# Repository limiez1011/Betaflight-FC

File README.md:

# yecnod F405 V1.1

## Description

open-source (not that anyone would want to use it) 40x40 F405 Flight controller using betaflight software.
## Features

- 3 Universal UARTS
- Dedicated pads for analog VTX
- 9V and 5V Buck converters
- 2x 3.3V LDOS
- Integrated barometer
- LDO and Buck converter status LEDS
- 16MB Blackbox flash
- Full betaflight support
- ICM 42688-P (kind of a flex with how hard they are to get nowadays)
- 4V5 Pads for RX

This is the first revision of the yecnodF405 so expect more features on the 2nd.

[Schematic PDF](https://github.com/user-attachments/files/29501861/20x20.fc.pdf)

## COST

- AROUND 60 USD PER PCB
- AROUND 30 USD FOR 5 PCBS

On my next revision I will try to cut the costs by atleast 40%

## BOM

|   | NAME        | PURPOSE                                | QTY | PRICE  | LINK                                                                                                                                                                                                                                                                                        |
|---|-------------|----------------------------------------|-----|--------|---------------------------------------------------------------------------------------------------------------------------------------------------------------------------------------------------------------------------------------------------------------------------------------------|
| 1 | LCSC        | PASSIVES/ALL IC'S                      | 1   | $73.43 | [LINK](https://www.lcsc.com)                                                                                                                                                                                                                                                                |
| 2 | HOT AIR GUN | SOLDERING                              | 1   | $35    | [LINK](https://www.emag.ro/fier-de-lipit-torta-cu-aer-cald-yihua-8858-iv-a5dc-582e4/pd/D3JM2VYBM/?ref=graph_profiled_similar_fallback_1_5&provider=rec&recid=rec_49_08c7c992410847fca068c8fe31b8623d8bb9a36b783f82e050163eaf2f512421_1786099721&scenario_ID=49)                             |
| 3 | MP4420      | BUCK CONVERTER (NOT AVAILABLE ON LCSC) | 10  | $7.7   | [LINK](https://www.aliexpress.com/item/1005009928983923.html?spm=a2g0o.cart.0.0.2e1938damlvGFl&mp=1)                                                                                                                                                                                        |
| 4 | TWEEZERS    | HELP FOR SOLDERING TINY 0402           | 2   | $16.5  | [LINK](https://www.aliexpress.com/item/1005007691201333.html?spm=a2g0o.cart.0.0.2e1938damlvGFl&mp=1&pdp_ext_f=%7B%22cart2PdpParams%22%3A%7B%22pdpBusinessMode%22%3A%22retail%22%7D%7D) [LINK](https://www.aliexpress.com/item/1005008389644631.html?spm=a2g0o.cart.0.0.2e1938damlvGFl&mp=1) |
| 5 | FLUX        | SOLDERING                              | 1   | $11.2  | [LINK](https://www.aliexpress.com/item/1005008666080401.html?spm=a2g0o.cart.0.0.2e1938damlvGFl&mp=1)                                                                                                                                                                                        |
| 6 | C245 TIP    | SOLDERING                              | 1   | $7     | [LINK](https://www.aliexpress.com/item/1005008666080401.html?spm=a2g0o.cart.0.0.2e1938damlvGFl&mp=1)                                                                                                                                                                                        |
| 7 | JLCPCB      | PCBS                                   | 5   | $12.71 | [LINK](https://jlcpcb.com/)                                                                                                                                                                                                                                                                 |
| 8 | TARIFFS     | dumb eu laws                           | 1   | $41    |                                                                                                                                                                                                                                                                                             |

Final prices for each website are available as screenshots on the macondo website. LCSC cart BOM is available as a csv. 
Total price for everything is 204.73 USD
## Notes

- This is my 2nd ever electronics project (Although I made another 3 during the break I took on this project) so don't expect everything to be electrically sound, this has been a great learning experience though, even with all the headaches it gave me.
- The jlcpcb BOM is only partly complete since I've decided to not use PCBA (use at you own risk some parts may not be right)

## Photos

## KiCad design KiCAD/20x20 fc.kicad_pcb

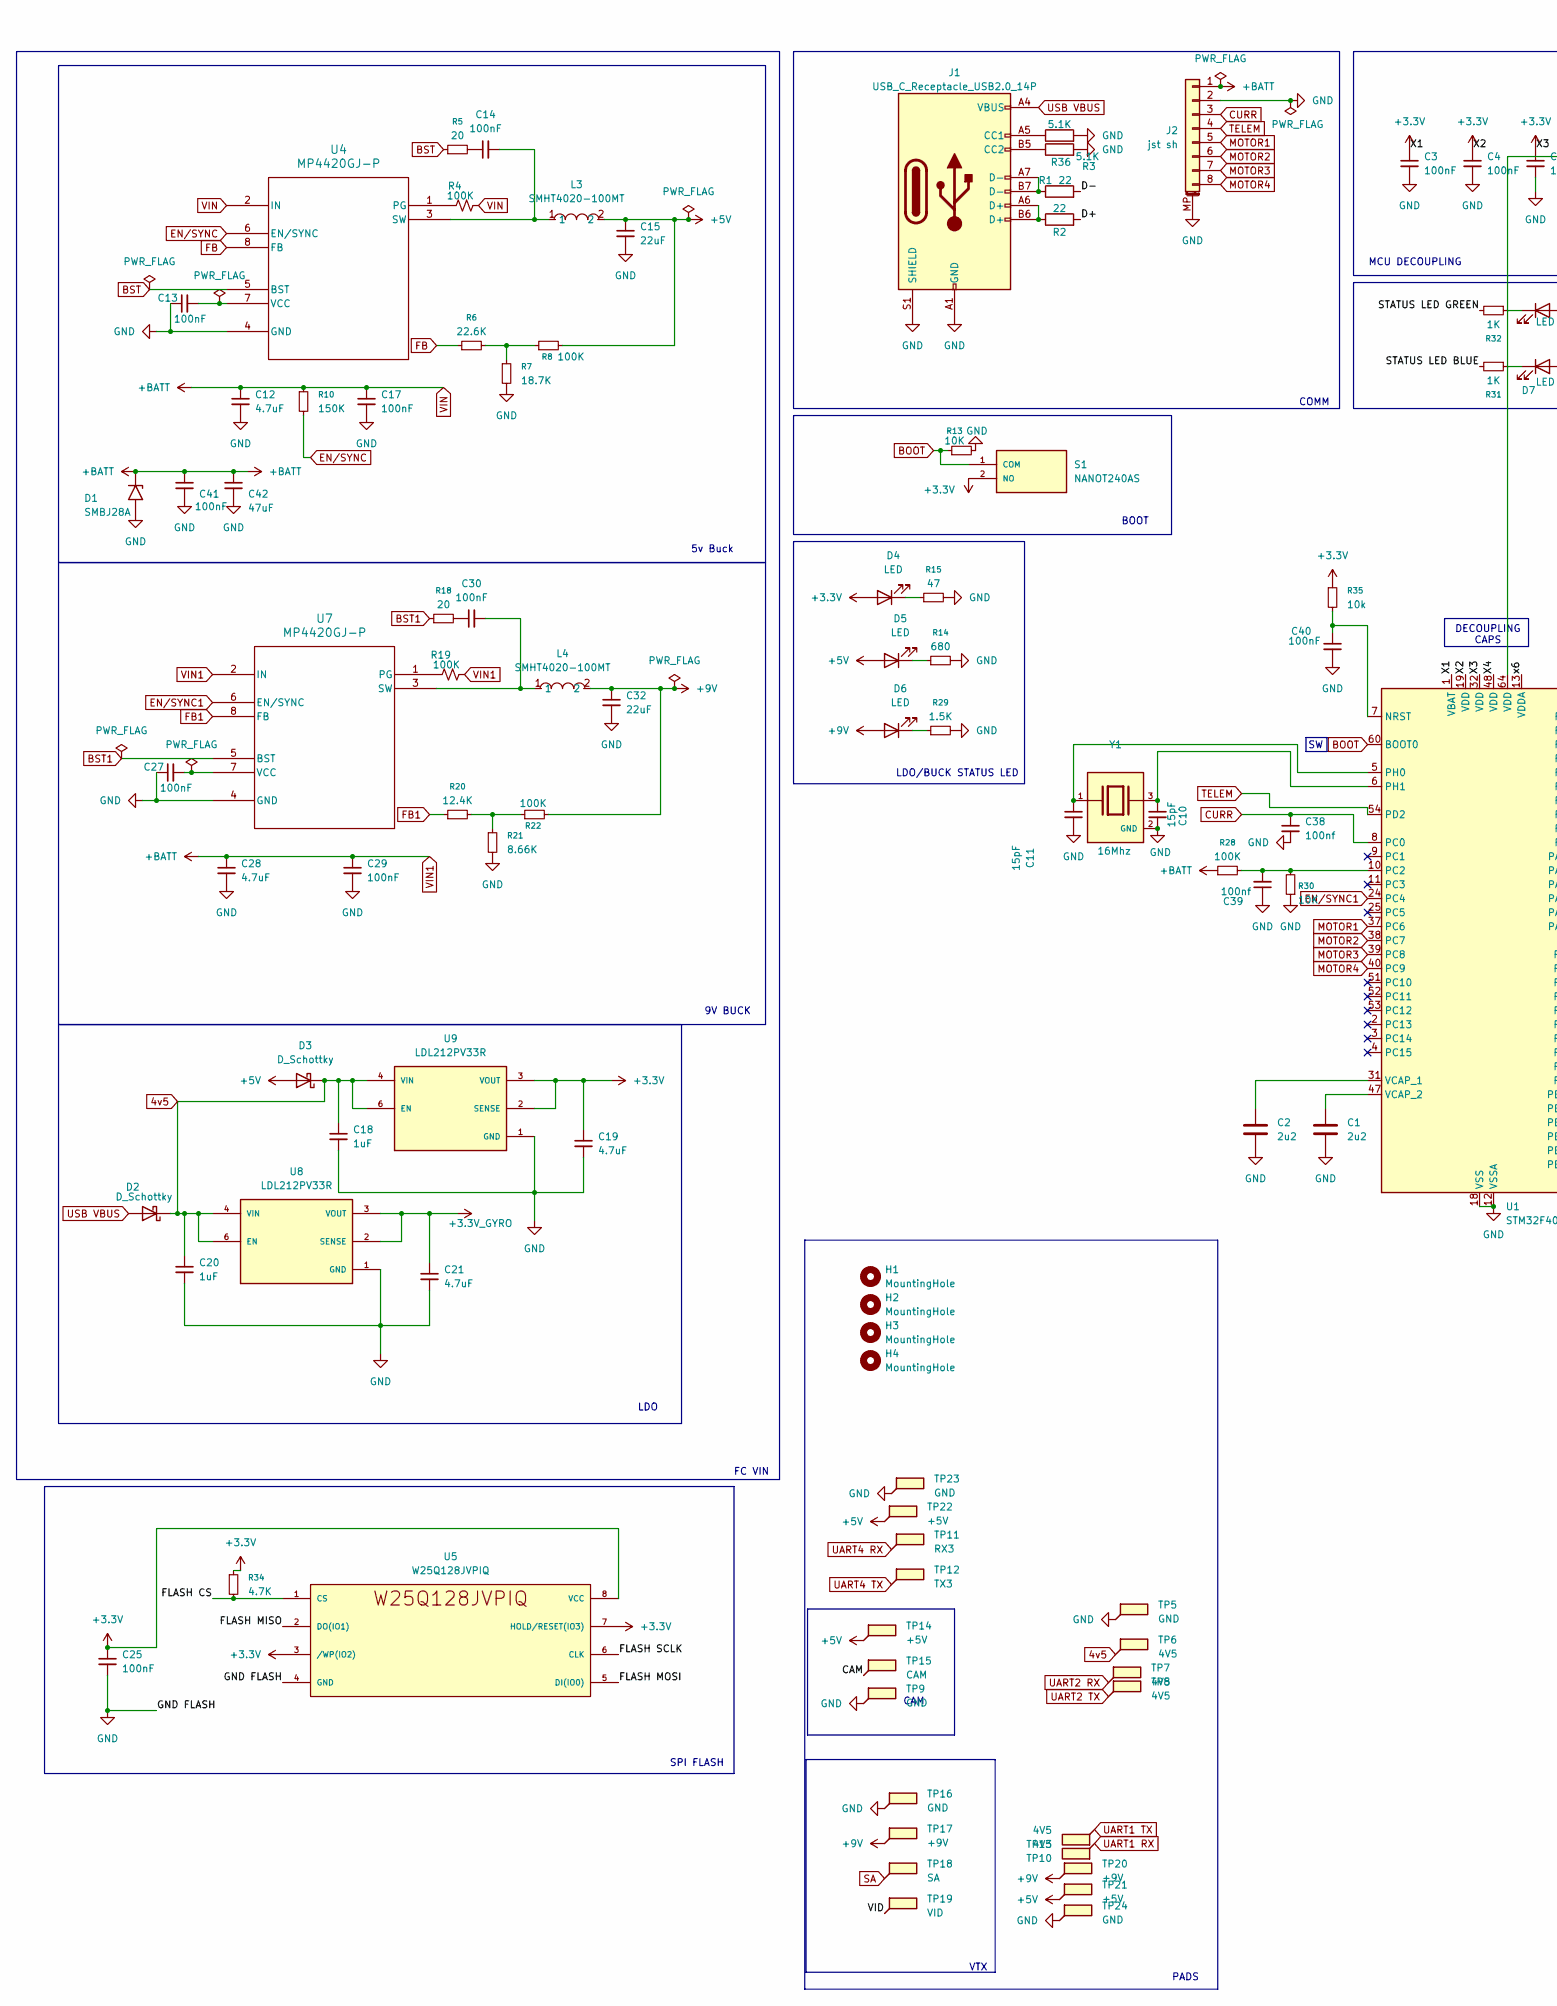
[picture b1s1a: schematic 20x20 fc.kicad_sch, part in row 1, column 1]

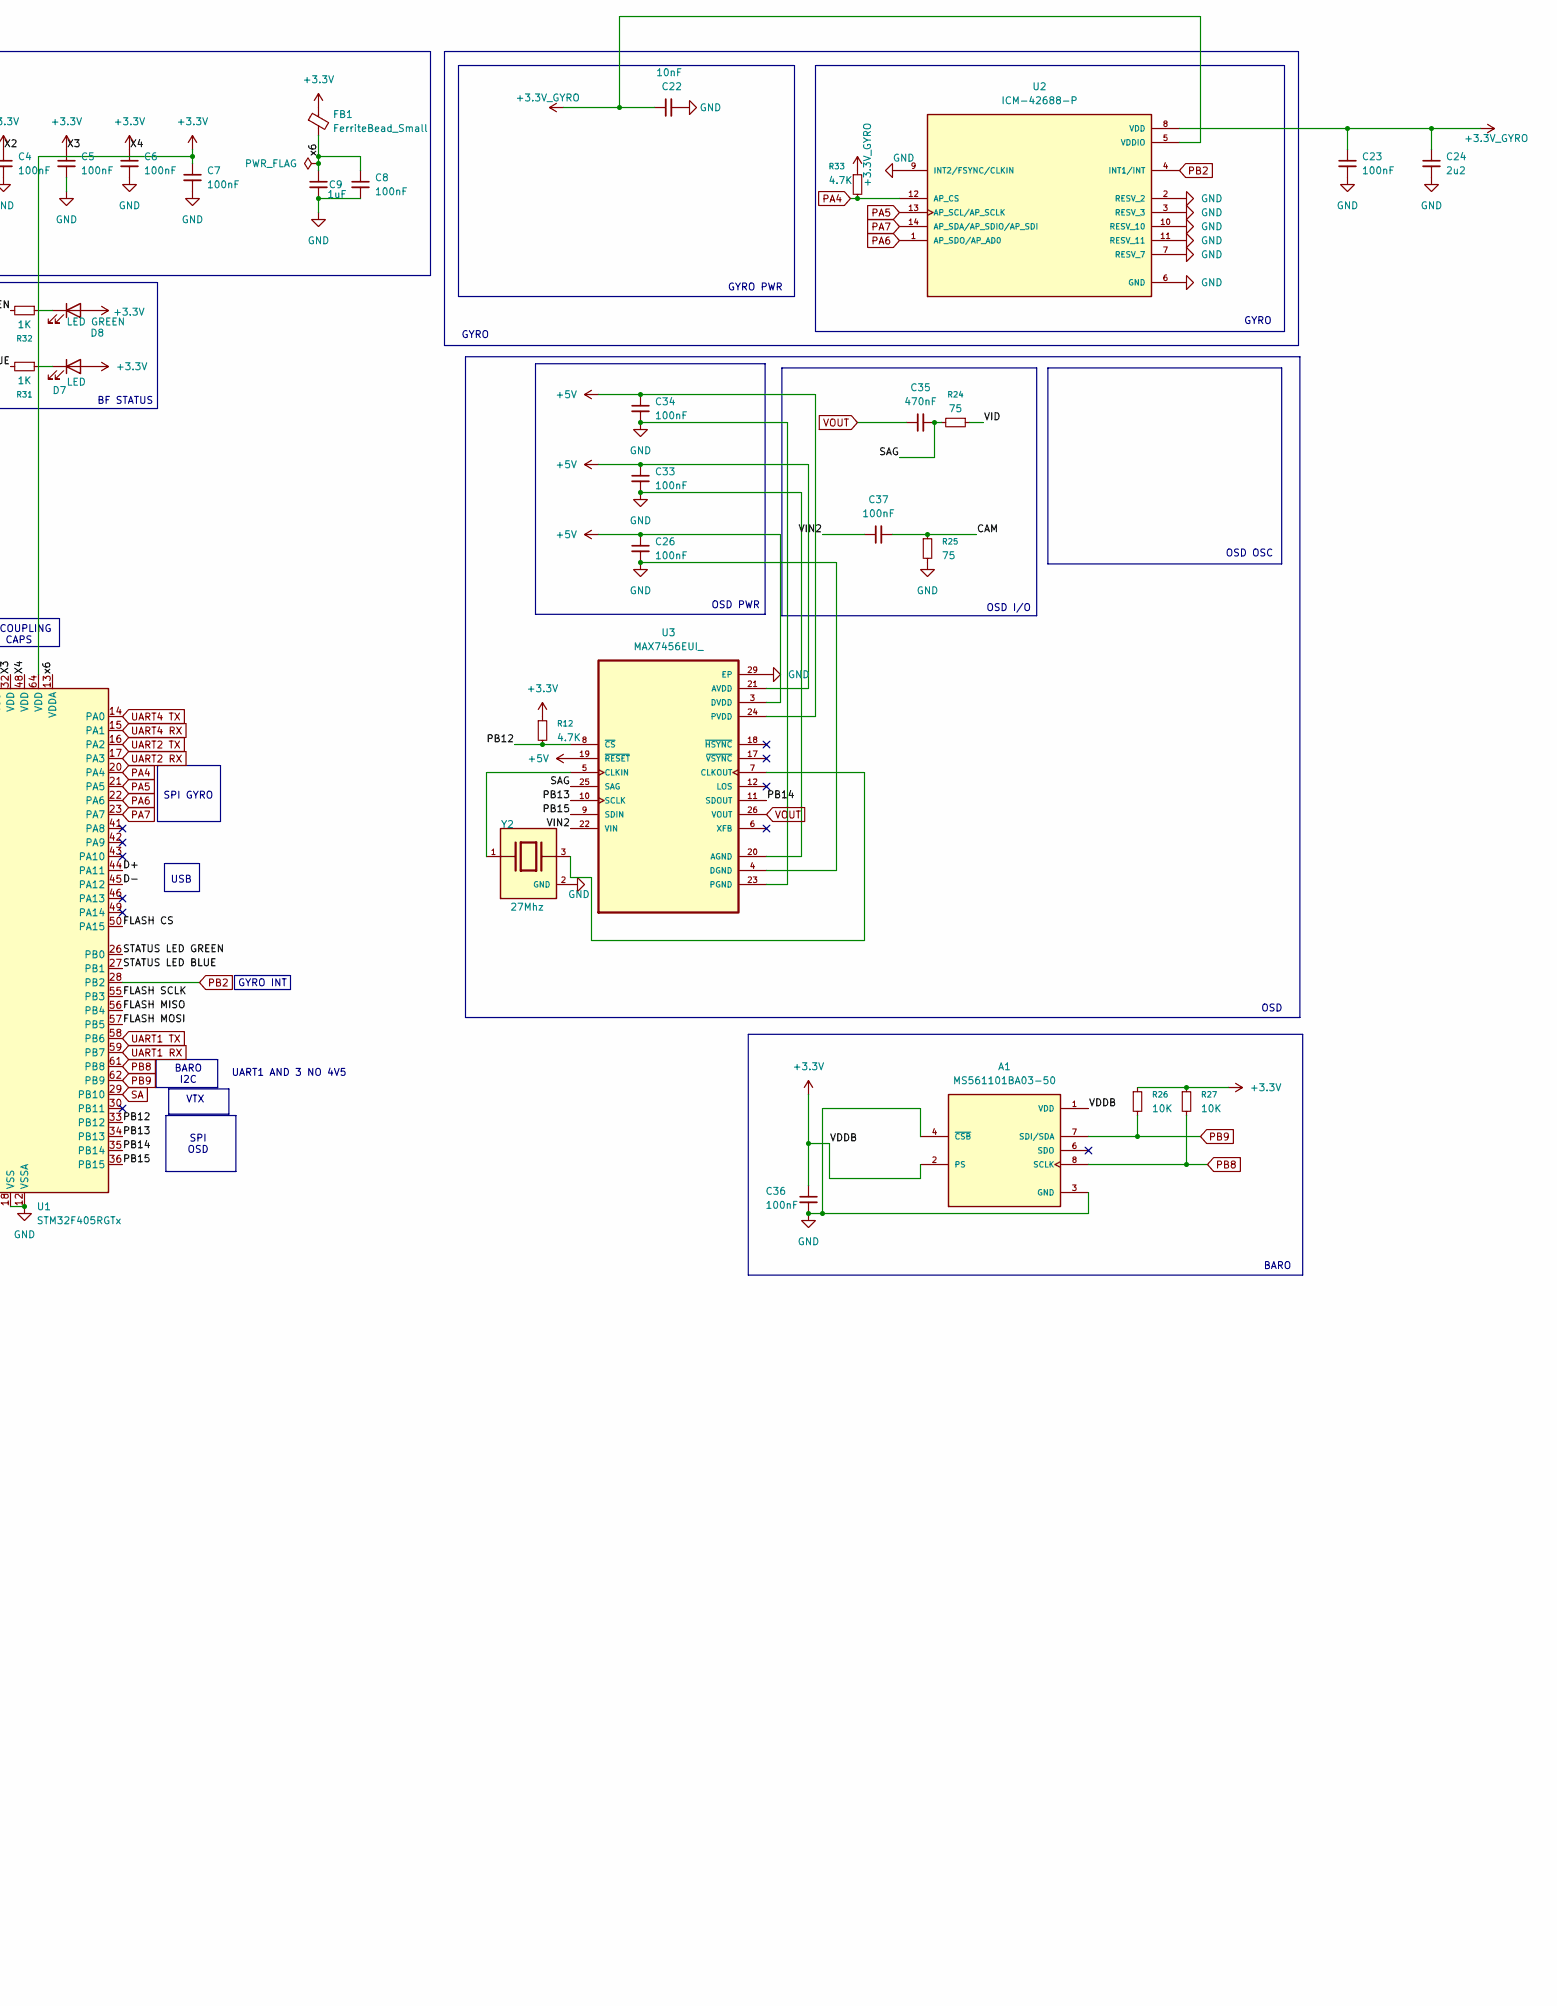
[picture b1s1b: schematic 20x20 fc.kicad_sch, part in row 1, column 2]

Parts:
A1: MS561101BA03-50; SENSORS-SMD_MS5611-01BA03; PARTREV 06/2017
C1, C2, C24: 2u2; C_0402_1005Metric
C3, C4, C5, C6, C7, C8, C13, C14, C23, C25, C26, C27, C30, C33, C34, C36, C37, C40: 100nF; C_0402_1005Metric
C9, C18, C20: 1uF; C_0402_1005Metric
C10, C11: 15pF; C_0402_1005Metric
C12, C28: 4.7uF; C_0805_2012Metric
C15, C32: 22uF; C_0805_2012Metric
C17, C29, C41: 100nF; C_0603_1608Metric
C19, C21: 4.7uF; C_0402_1005Metric
C22: 10nF; C_0402_1005Metric
C35: 470nF; C_0402_1005Metric
C38, C39: 100nf; C_0402_1005Metric
C42: 47uF; C_1206_3216Metric
D1: SMBJ28A; D_SMA
D2, D3: D_Schottky; D_0603_1608Metric
D4, D5, D6, D7: LED; LED_0603_1608Metric
D8: LED GREEN; LED_0603_1608Metric
FB1: FerriteBead_Small; L_0402_1005Metric
H1, H2, H3, H4: MountingHole; MountingHole_4.3mm_M4
J1: USB_C_Receptacle_USB2.0_14P; USB_C_Receptacle_HRO_TYPE-C-31-M-12
J2: jst sh; JST_SH_SM08B-SRSS-TB_1x08-1MP_P1.00mm_Horizontal
L3, L4: SMHT4020-100MT; IND-SMD_L4.0-W4.0_TNR4030S; MPN SMHT4020-100MT; LCSC Part C42924178
R1, R2: 22; R_0402_1005Metric
R3, R36: 5.1K; R_0402_1005Metric
R4, R8, R19, R22, R28: 100K; R_0402_1005Metric
R5, R18: 20; R_0402_1005Metric
R6: 22.6K; R_0402_1005Metric
R7: 18.7K; R_0402_1005Metric
R10: 150K; R_0402_1005Metric
R12, R33, R34: 4.7K; R_0402_1005Metric
R13, R26, R27, R30: 10K; R_0402_1005Metric
R14: 680; R_0402_1005Metric
R15: 47; R_0402_1005Metric
R20: 12.4K; R_0402_1005Metric
R21: 8.66K; R_0402_1005Metric
R24, R25: 75; R_0402_1005Metric
R29: 1.5K; R_0402_1005Metric
R31, R32: 1K; R_0402_1005Metric
R35: 10k; R_0402_1005Metric
S1: NANOT240AS; MANUFACTURER_PART_NUMBER NANOT240AS
TP5, TP9, TP16, TP23, TP24: GND; 1.5mm pad
TP6, TP7, TP8, TP10, TP13: 4V5; 1.5mm pad
TP11: RX3; 1.5mm pad
TP12: TX3; 1.5mm pad
TP14, TP21, TP22: +5V; 1.5mm pad
TP15: CAM; 1.5mm pad
TP17, TP20: +9V; 1.5mm pad
TP18: SA; 1.5mm pad
TP19: VID; 1.5mm pad
U1: STM32F405RGTx; LQFP-64_10x10mm_P0.5mm
U2: ICM-42688-P; LGA-14_L3.0-W2.5-P0.50-TL; PARTREV 1.2
U3: MAX7456EUI_; TSSOP-28_L9.7-W4.4-P0.65-LS6.4-BL-EP-2
U4, U7: MP4420GJ-P; TSOT-23-8_L2.9-W1.6-P0.65-LS2.8-BL
U5: W25Q128JVPIQ; WSON-8_L6.0-W5.0-P1.27-BL-EP
U8, U9: LDL212PV33R; DFN-6_L2.0-W2.0-P0.50-BL-EP1.45; PARTREV 5
Y1: 16Mhz; CRYSTAL-SMD_4P-L2.0-W1.6-BL; PARTREV 06.19.15
Y2: 27Mhz; CRYSTAL-SMD_4P-L2.0-W1.6-BL; PARTREV 06.19.15

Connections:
4v5: C18.1, C20.1, D2.1 (K), D3.1 (K), TP6.1 (1_1), U8.4 (VIN), U8.6 (EN), U9.4 (VIN), U9.6 (EN)
+3.3V: A1.1 (VDD), A1.2 (PS), C3.1, C4.1, C5.1, C6.1, C7.1, C19.1, C25.1, C36.1, D4.2 (A), D7.2 (A), D8.2 (A), FB1.1, R12.1, R26.1, R27.1, R34.1, R35.1, S1.2 (NO), U1.1 (VBAT), U1.19 (VDD), U1.32 (VDD), U1.48 (VDD), U1.64 (VDD), U5.3 (/WP(IO2)), U5.7 (HOLD/RESET(IO3)), U5.8 (VCC), U9.2 (SENSE), U9.3 (VOUT)
+3.3V_GYRO: C21.1, C22.1, C23.1, C24.1, R33.1, U2.5 (VDDIO), U2.8 (VDD), U8.2 (SENSE), U8.3 (VOUT)
+5V: C15.1, C26.1, C33.1, C34.1, D3.2 (A), D5.2 (A), L3.2, R8.2, TP14.1 (1_1), TP21.1 (1_1), TP22.1 (1_1), U3.3 (DVDD), U3.19 (~RESET), U3.21 (AVDD), U3.24 (PVDD)
+9V: C32.1, D6.2 (A), L4.2, R22.2, TP17.1 (1_1), TP20.1 (1_1)
/CAM: C37.2, R25.1, TP15.1 (1_1)
/D+: R2.2, U1.44 (PA11)
/D-: R1.2, U1.45 (PA12)
/FLASH CS: R34.2, U1.50 (PA15), U5.1 (CS)
/FLASH MISO: U1.56 (PB4), U5.2 (DO(IO1))
/FLASH MOSI: U1.57 (PB5), U5.5 (DI(IO0))
/FLASH SCLK: U1.55 (PB3), U5.6 (CLK)
/PB12: R12.2, U1.33 (PB12), U3.8 (~CS)
/PB13: U1.34 (PB13), U3.10 (SCLK)
/PB14: U1.35 (PB14), U3.11 (SDOUT)
/PB15: U1.36 (PB15), U3.9 (SDIN)
/SAG: C35.2, R24.2, U3.25 (SAG)
/STATUS LED BLUE: R31.2, U1.27 (PB1)
/STATUS LED GREEN: R32.2, U1.26 (PB0)
/VID: R24.1, TP19.1 (1_1)
/VIN2: C37.1, U3.22 (VIN)
/x6: C8.1, C9.1, FB1.2, U1.13 (VDDA)
BOOT: R13.1, S1.1 (COM), U1.60 (BOOT0)
BST: R5.1, U4.5 (BST)
BST1: R18.1, U7.5 (BST)
CURR: C38.1, J2.3, U1.8 (PC0)
EN/SYNC: R10.2, U4.6 (EN/SYNC)
EN/SYNC1: U1.24 (PC4), U7.6 (EN/SYNC)
FB: R6.1, U4.8 (FB)
FB1: R20.1, U7.8 (FB)
GND: A1.3 (GND), A1.4 (~CSB), A1.5 (~CSB), C1.2, C2.2, C3.2, C4.2, C5.2, C6.2, C7.2, C8.2, C9.2, C10.2, C11.2, C12.2, C13.1, C15.2, C17.2, C18.2, C19.2, C20.2, C21.2, C22.2, C23.2, C24.2, C25.2, C26.2, C27.1, C28.2, C29.2, C32.2, C33.2, C34.2, C36.2, C38.2, C39.1, C40.2, C41.2, C42.2, D1.2 (A2), J1.A1 (GND), J1.A12 (GND), J1.B1 (GND), J1.B12 (GND), J1.S1 (SHIELD), J2.2, J2.MP (MountPin), R3.2, R7.2, R13.2, R14.2, R15.2, R21.2, R25.2, R29.2, R30.1, R36.2, TP5.1 (1_1), TP9.1 (1_1), TP16.1 (1_1), TP23.1 (1_1), TP24.1 (1_1), U1.12 (VSSA), U1.18 (VSS), U1.63 (VSS), U2.2 (RESV_2), U2.3 (RESV_3), U2.6 (GND), U2.7 (RESV_7), U2.9 (INT2/FSYNC/CLKIN), U2.10 (RESV_10), U2.11 (RESV_11), U3.4 (DGND), U3.20 (AGND), U3.23 (PGND), U3.29 (EP), U4.4 (GND), U5.4 (GND), U5.9 (GND), U7.4 (GND), U8.1 (GND), U8.7 (GND), U9.1 (GND), U9.7 (GND), Y1.2 (GND), Y1.4 (GND), Y2.2 (GND), Y2.4 (GND)
MOTOR1: J2.5, U1.37 (PC6)
MOTOR2: J2.6, U1.38 (PC7)
MOTOR3: J2.7, U1.39 (PC8)
MOTOR4: J2.8, U1.40 (PC9)
unnamed: C14.1, R5.2
unnamed: C30.1, R18.2
unnamed: D4.1 (K), R15.1
unnamed: D5.1 (K), R14.1
unnamed: D6.1 (K), R29.1
unnamed: D7.1 (K), R31.1
unnamed: D8.1 (K), R32.1
unnamed: J1.A5 (CC1), R3.1
unnamed: J1.B5 (CC2), R36.1
unnamed: J1.A6 (D+), J1.B6 (D+), R2.1
unnamed: J1.A7 (D-), J1.B7 (D-), R1.1
unnamed: R6.2, R7.1, R8.1
unnamed: R20.2, R21.1, R22.1
unnamed: C40.1, R35.2, U1.7 (NRST)
unnamed: C39.2, R28.2, R30.2, U1.10 (PC2)
unnamed: C11.1, U1.5 (PH0), Y1.1
unnamed: C10.1, U1.6 (PH1), Y1.3
unnamed: C2.1, U1.31 (VCAP_1)
unnamed: C1.1, U1.47 (VCAP_2)
unnamed: U3.5 (CLKIN), Y2.1
unnamed: U3.7 (CLKOUT), Y2.3
unnamed: R4.1, U4.1 (PG)
unnamed: C14.2, L3.1, U4.3 (SW)
unnamed: C13.2, U4.7 (VCC)
unnamed: R19.1, U7.1 (PG)
unnamed: C30.2, L4.1, U7.3 (SW)
unnamed: C27.2, U7.7 (VCC)
PA4: R33.2, U1.20 (PA4), U2.12 (AP_CS)
PA5: U1.21 (PA5), U2.13 (AP_SCL/AP_SCLK)
PA6: U1.22 (PA6), U2.1 (AP_SDO/AP_AD0)
PA7: U1.23 (PA7), U2.14 (AP_SDA/AP_SDIO/AP_SDI)
PB2: U1.28 (PB2), U2.4 (INT1/INT)
PB8: A1.8 (SCLK), R27.2, U1.61 (PB8)
PB9: A1.7 (SDI/SDA), R26.2, U1.62 (PB9)
SA: TP18.1 (1_1), U1.29 (PB10)
TELEM: J2.4, U1.54 (PD2)
UART1 RX: TP10.1 (1_1), U1.59 (PB7)
UART1 TX: TP13.1 (1_1), U1.58 (PB6)
UART2 RX: TP7.1 (1_1), U1.17 (PA3)
UART2 TX: TP8.1 (1_1), U1.16 (PA2)
UART4 RX: TP11.1 (1_1), U1.15 (PA1)
UART4 TX: TP12.1 (1_1), U1.14 (PA0)
USB VBUS: D2.2 (A), J1.A4 (VBUS), J1.A9 (VBUS), J1.B4 (VBUS), J1.B9 (VBUS)
VIN: C12.1, C17.1, C28.1, C29.1, C41.1, C42.1, D1.1 (A1), J2.1, R4.2, R10.1, R19.2, R28.1, U4.2 (IN), U7.2 (IN)
VOUT: C35.1, U3.26 (VOUT)

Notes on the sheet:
GYRO PWR
CAM
OSD OSC
GYRO
LDO/BUCK STATUS LED
OSD PWR
COMM
BOOT
PADS
BARO I2C
MCU DECOUPLING
FC VIN
SPI OSD
OSD
9V BUCK
BF STATUS
SPI FLASH
VTX
SPI GYRO
OSD I/O
LDO
GYRO INT
BARO
5v Buck
UART1 AND 3 NO 4V5
DECOUPLING CAPS
USB

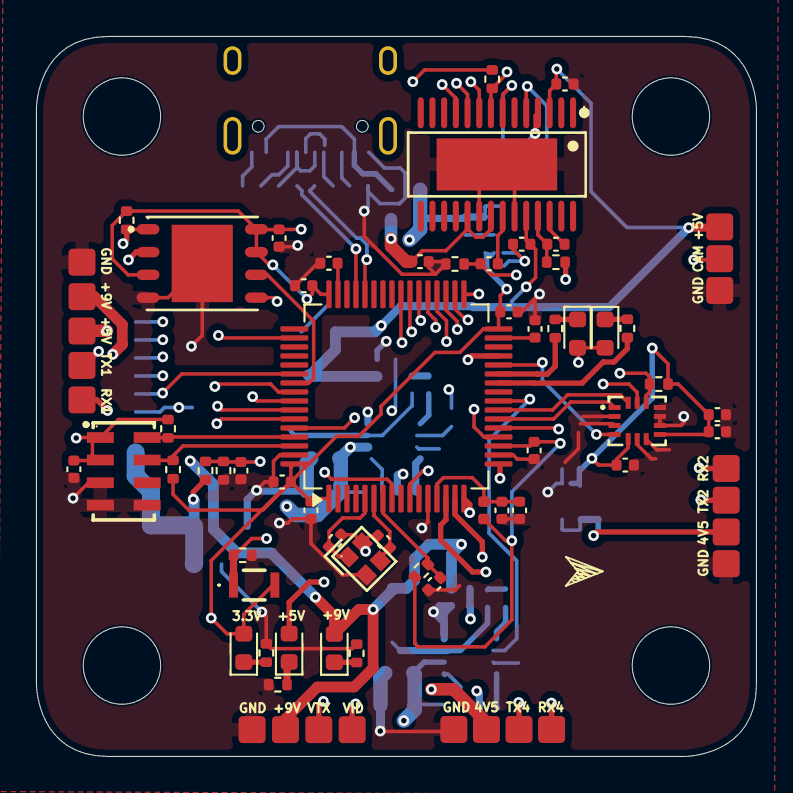
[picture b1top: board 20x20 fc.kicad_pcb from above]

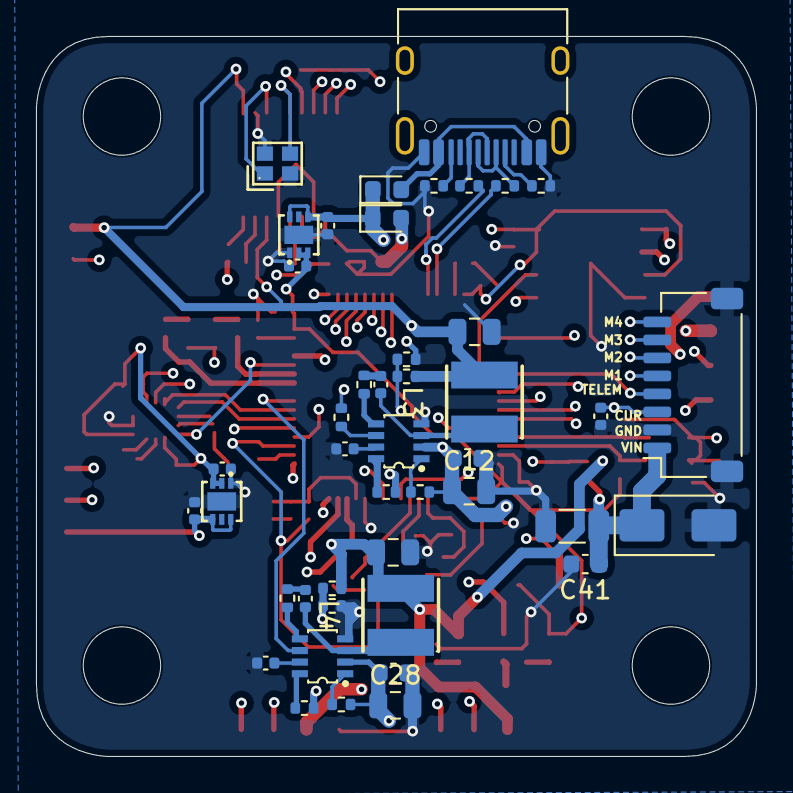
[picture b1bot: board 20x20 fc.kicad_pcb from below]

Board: 6 copper layers, 40.0 x 40.0 mm, 120 parts (44 on the bottom side), 80 nets.

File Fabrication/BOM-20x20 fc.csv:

Comment,Designator,Footprint,LCSC,Quantity
1.5K,R29,R_0402_1005Metric,C25867,1
100K,"R19,R22,R28,R4,R8",R_0402_1005Metric,C25741,5
100nF,"C17,C29,C41",C_0603_1608Metric,C14663,3
100nF,"C13,C14,C23,C25,C26,C27,C3,C30,C33,C34,C36,C37,C4,C40,C5,C6,C7,C8",C_0402_1005Metric,C307331,18
100nf,"C38,C39",C_0402_1005Metric,C307331,2
10K,"R13,R26,R27,R30",R_0402_1005Metric,C25744,4
10k,R35,R_0402_1005Metric,C25744,1
10nF,C22,C_0402_1005Metric,C15195,1
12.4K,R20,R_0402_1005Metric,C11692,1
150K,R10,R_0402_1005Metric,C25755,1
15pF,"C10,C11",C_0402_1005Metric,C1548,2
16Mhz,Y1,CRYSTAL-SMD_4P-L2.0-W1.6-BL,C1985520,1
18.7K,R7,R_0402_1005Metric,C11476,1
1K,"R31,R32",R_0402_1005Metric,C11702,2
1uF,"C18,C20,C9",C_0402_1005Metric,C1518208,3
20,"R18,R5",R_0402_1005Metric,C25150,2
22,"R1,R2",R_0402_1005Metric,C25092,2
22.6K,R6,R_0402_1005Metric,C477674,1
22uF,"C15,C32",C_0805_2012Metric,C45783,2
27Mhz,Y2,CRYSTAL-SMD_4P-L2.0-W1.6-BL,C1985480,1
2u2,"C1,C2,C24",C_0402_1005Metric,C12530,3
4.7K,"R12,R33,R34",R_0402_1005Metric,C25900,3
4.7uF,"C19,C21",C_0402_1005Metric,C2858031,2
4.7uF,"C12,C28",C_0805_2012Metric,C98192,2
47,R15,R_0402_1005Metric,C25118,1
470nF,C35,C_0402_1005Metric,C47339,1
47uF,C42,C_1206_3216Metric,C76659,1
5.1K,"R3,R36",R_0402_1005Metric,C25905,2
680,R14,R_0402_1005Metric,C137948,1
75,"R24,R25",R_0402_1005Metric,C2909384,2
8.66K,R21,R_0402_1005Metric,C5126133,1
D_Schottky,"D2,D3",D_0603_1608Metric,C151629,2
FerriteBead_Small,FB1,L_0402_1005Metric,C160977,1
ICM-42688-P,U2,LGA-14_L3.0-W2.5-P0.50-TL,C1850418,1
LDL212PV33R,"U8,U9",DFN-6_L2.0-W2.0-P0.50-BL-EP1.45,C2969892,2
LED,"D4,D5,D6,D7",LED_0603_1608Metric,C2288,4
LED GREEN,D8,LED_0603_1608Metric,C12624,1
MAX7456EUI_,U3,TSSOP-28_L9.7-W4.4-P0.65-LS6.4-BL-EP-2,C82351,1
MP4420GJ-P,"U4,U7",TSOT-23-8_L2.9-W1.6-P0.65-LS2.8-BL,C3194330,2
MS561101BA03-50,A1,SENSORS-SMD_MS5611-01BA03,C15639,1
SMBJ28A,D1,D_SMA,C19077582,1
SMHT4020-100MT,"L3,L4",IND-SMD_L4.0-W4.0_TNR4030S,C42924178,2
STM32F405RGTx,U1,LQFP-64_10x10mm_P0.5mm,C2054141,1
USB_C_Receptacle_USB2.0_14P,J1,USB_C_Receptacle_HRO_TYPE-C-31-M-12,C165948,1
W25Q128JVPIQ,U5,WSON-8_L6.0-W5.0-P1.27-BL-EP,C190862,1
jst sh,J2,JST_SH_SM08B-SRSS-TB_1x08-1MP_P1.00mm_Horizontal,C160407,1
RX3,TP11,1.5mm pad,,1
GND,TP24,1.5mm pad,,1
+5V,TP21,1.5mm pad,,1
GND,TP16,1.5mm pad,,1
+9V,TP17,1.5mm pad,,1
GND,TP23,1.5mm pad,,1
+5V,TP14,1.5mm pad,,1
CAM,TP15,1.5mm pad,,1
GND,TP9,1.5mm pad,,1
4V5,TP8,1.5mm pad,,1
GND,TP5,1.5mm pad,,1
VID,TP19,1.5mm pad,,1
4V5,TP13,1.5mm pad,,1
4V5,TP10,1.5mm pad,,1
SA,TP18,1.5mm pad,,1
+5V,TP22,1.5mm pad,,1
+9V,TP20,1.5mm pad,,1
4V5,TP6,1.5mm pad,,1
TX3,TP12,1.5mm pad,,1
NANOT240AS,S1,NANOT240AS,,1
4V5,TP7,1.5mm pad,,1

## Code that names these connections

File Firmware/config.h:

/*
 * This file is part of Betaflight.
 *
 * Betaflight is free software. You can redistribute this software
 * and/or modify this software under the terms of the GNU General
 * Public License as published by the Free Software Foundation,
 * either version 3 of the License, or (at your option) any later
 * version.
 *
 * Betaflight is distributed in the hope that it will be useful,
 * but WITHOUT ANY WARRANTY; without even the implied warranty of
 * MERCHANTABILITY or FITNESS FOR A PARTICULAR PURPOSE.
 *
 * See the GNU General Public License for more details.
 *
 * You should have received a copy of the GNU General Public
 * License along with this software.
 *
 * If not, see <http://www.gnu.org/licenses/>.
 */

#pragma once

#define FC_TARGET_MCU     STM32F405
#define BOARD_NAME        yecnodF405
#define MANUFACTURER_ID   CUST

#define USE_GYRO
#define USE_GYRO_SPI_ICM42688P

#define USE_ACC
#define USE_ACC_SPI_ICM42688P

#define USE_BARO
#define USE_BARO_MS5611

#define USE_FLASH
#define USE_FLASH_W25Q128FV
#define USE_MAX7456

#define MOTOR1_PIN           PC6
#define MOTOR2_PIN           PC7
#define MOTOR3_PIN           PC8
#define MOTOR4_PIN           PC9

#define UART1_TX_PIN         PB6
#define UART1_RX_PIN         PB7
#define UART2_TX_PIN         PA2
#define UART2_RX_PIN         PA3
#define UART3_TX_PIN         PB10
#define UART4_TX_PIN         PA0
#define UART4_RX_PIN         PA1
#define UART5_RX_PIN         PD2

#define I2C1_SCL_PIN         PB8
#define I2C1_SDA_PIN         PB9



#define SPI1_SCK_PIN         PA5
#define SPI1_SDO_PIN         PA7
#define SPI1_SDI_PIN         PA6
#define GYRO_1_CS_PIN        PA4
#define GYRO_1_EXTI_PIN      PB2	
#define GYRO_1_SPI_INSTANCE	 SPI1


#define SPI2_SCK_PIN         PB13
#define SPI2_SDI_PIN         PB15
#define SPI2_SDO_PIN         PB14
#define MAX7456_SPI_CS_PIN   PB12
#define MAX7456_SPI_INSTANCE SPI2

#define SPI3_SCK_PIN         PB3
#define SPI3_SDI_PIN         PB4
#define SPI3_SDO_PIN         PB5
#define FLASH_CS_PIN         PA15
#define FLASH_SPI_INSTANCE   SPI3


#define ADC_VBAT_PIN         PC2
#define ADC_CURR_PIN         PC0

#define LED0_PIN             PB1
#define LED1_PIN             PB0


#define TIMER_PIN_MAPPING \
    TIMER_PIN_MAP(0, MOTOR1_PIN, 2, 0) \
    TIMER_PIN_MAP(1, MOTOR2_PIN, 2, 1) \
    TIMER_PIN_MAP(2, MOTOR3_PIN, 2, 1) \
    TIMER_PIN_MAP(3, MOTOR4_PIN, 2, 0) \

#define ADC3_DMA_OPT 1
#define ADC_INSTANCE ADC3

#define BARO_I2C_INSTANCE I2CDEV_1

#define DEFAULT_BLACKBOX_DEVICE BLACKBOX_DEVICE_FLASH
#define DEFAULT_DSHOT_BITBANG           DSHOT_BITBANG_OFF

#define DEFAULT_CURRENT_METER_SOURCE CURRENT_METER_ADC
#define DEFAULT_VOLTAGE_METER_SOURCE VOLTAGE_METER_ADC
#define DEFAULT_VOLTAGE_METER_SCALE 110
#define SYSTEM_HSE_MHZ 16

#define ESC_SENSOR_UART      SERIAL_PORT_UART5

#define PINIO1_PIN PC4
#define PINIO1_BOX     40
#define PINIO1_CONFIG  129
#define BOX_USER1_NAME "10V BEC"

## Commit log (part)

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2026-05-16 Add configuration file for Betaflight firmware
2026-05-16 Add README.md file
2026-05-17 Add photos section to README.md
2026-05-17 Update README with project details and images
    Added detailed description, features, cost, and photos.
2026-05-17 Create x
2026-05-17 Add project notes and BOM information to README
    Added notes about the project experience and BOM status.
2026-05-17 Add project notes and update image section
    Added notes about project experience and BOM completeness.
2026-05-17 Revise header levels and enhance README clarity
    Updated section headers and improved formatting in README.
2026-05-17 Fix links and formatting in BOM section
    Updated links for solder paste, squeegee, and flux paste entries.
2026-05-17 Correct wording in README description
2026-05-17 Update README with revision notes and cost estimates
    Added notes about future revisions and cost reductions.
2026-06-30 Add images to README Photos section
    Added two new images to the Photos section of the README.
2026-06-30 Add schematic PDF link and update cost section
    Updated README to include schematic PDF link and revised content.
2026-06-30 Clean up BOM section and project notes in README
    Removed detailed BOM entries and notes from the README.
2026-06-30 Add new configuration defines for PINIO1
